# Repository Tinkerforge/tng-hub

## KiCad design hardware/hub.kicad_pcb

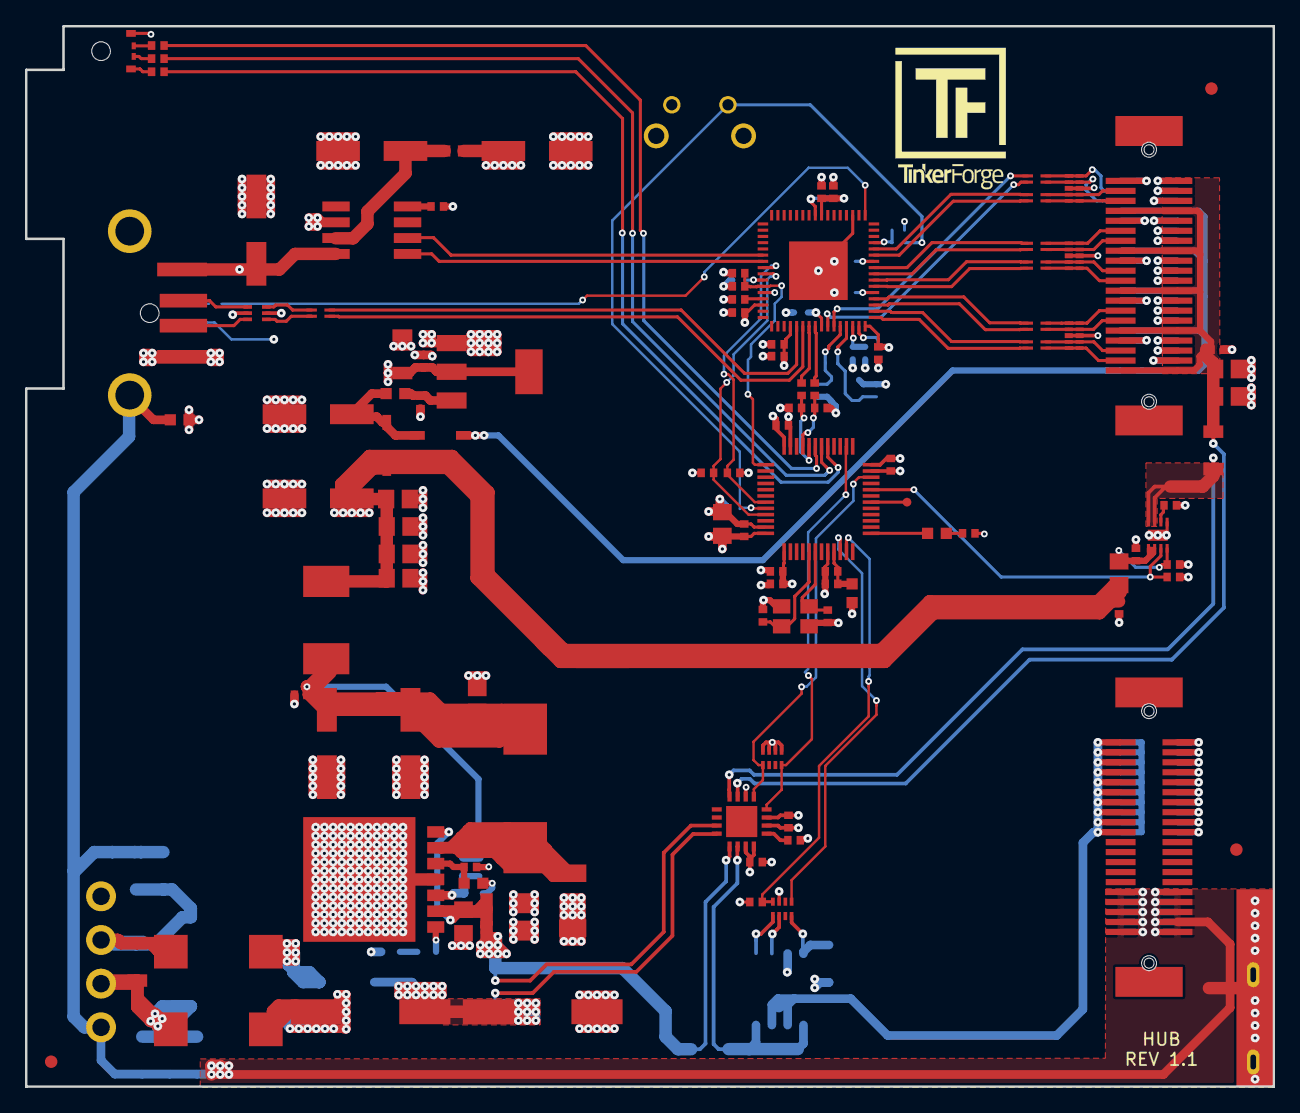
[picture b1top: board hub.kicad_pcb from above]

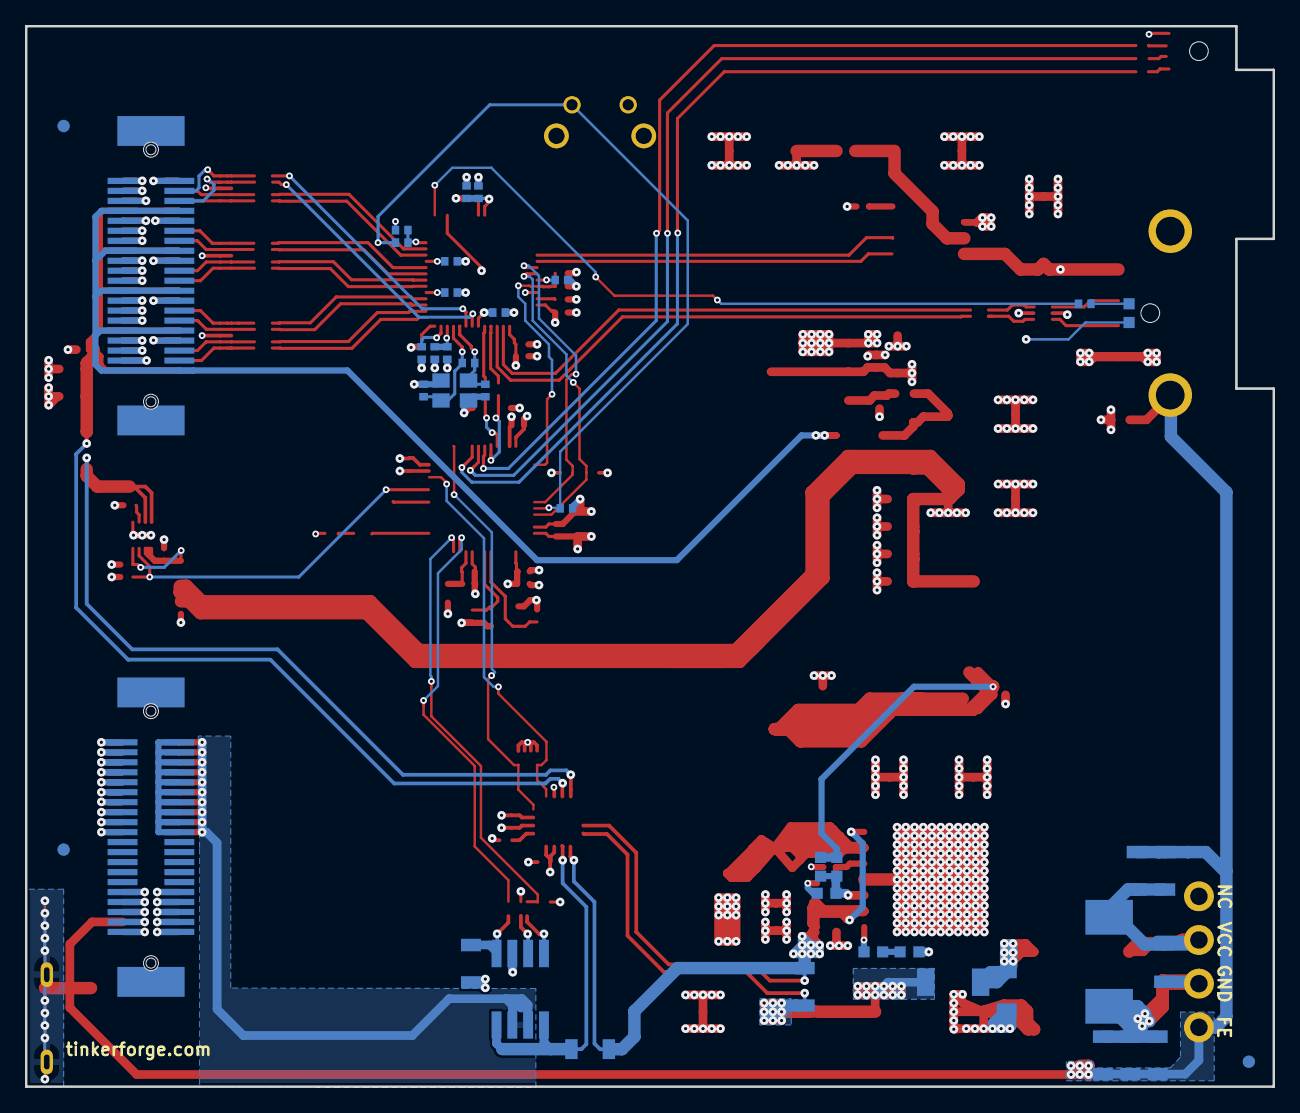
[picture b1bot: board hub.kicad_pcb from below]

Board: 4 copper layers, 100.0 x 85.0 mm, 152 parts (41 on the bottom side), 99 nets.

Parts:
C101, C102, C137, C138: 33pF; C0402F
C103, C105, C115, C119, C123, C124, C125, C126, C128, C134, C209, C226: 1uF; C0402F
C104, C106, C107, C110, C111, C112, C113, C114, C116, C118, C127, C129, C130, C131, C133, C214, C221, C222: 100nF; C0402F
C108, C109, C117, C203, C216, C219, C220: 100uF; ELKO_63
C120: 100nF; C0603F
C121, C122: 47pF; C0402F
C132: DNP; C0402F
C135, C136, C139, C215, C218, C223, C224, C225: 10uF; C0805E
C201, C202: 10uF/35V; C1206
C204, C211: 10nF; C1206
C205: 100nF/35V; C0805E
C206, C207: 1nF 2kV; C1206
C208: 100pF; C0402F
C210: 4.7nF; C0603F
C212, C213: UWT1H221MNL1GS; ELKO_103
C217: DNP; C0603F
C227: 10uF; C1206
D101: LED green; LED-LP
D102: LED; D0603F
D201: 3.0SMI30CATR; SMC
D202, D203: B0520LW-7-F; SOD-123
D205, D206: PMEG6045; SOD-128
Fiducial_Mark: VAL**; Fiducial_Mark
Fiducial_Mark#2, Fiducial_Mark#3, Fiducial_Mark#4, Fiducial_Mark#5, Fiducial_Mark#6: VAL**; Fiducial_Mark
J101: USB-A; USB-A-SMT-8231
J102: TNG-Power-BTM; TNG-40-BTM
J103: TNG-Power-TOP; TNG-40-TOP
J104: TNG-Data-BTM; TNG-40-BTM
J105: TNG-Data-TOP; TNG-40-TOP
L101, L201: INDUCTs; R0603F
L102, L103, L104, L105, L106, L107, L110: 744230900; WE-CNSW-0603
L108: FB; R0603F
L109: 742792040; R0805E
L202: 22uH 74437368220; WE-LHMI
L203: 10uH; SRP7030
LED101: EASV3015RGBA0; LED-RGB-LP
P101: Debug; DEBUG_PAD
P102: PE; PE_Hook
P202: PWR IN; OQ_4P
R101, R105, R106, R107, R109, R111, R116, R117, R218: 10k; R0402F
R102: 100k; R0402F
R103: 1M; R0402F
R104, R108, R114, R121: 1k; R0402F
R110: 12k; R0402F
R112, R113: 22; R0402F
R115, R119: 0; R0402F
R118: 1k; R1206
R120: 56; R0402F
R204, R206, R207: VC1206K201R030; R1206
R208: 27k; R0603F
R209: 1M; R1206
R212: 20k; R0603F
R214: 47k; R0603F
R215: 8.2k; R0603F
R219, R220, R221: 0.02; R1206
RP102, RP201: 10k; 4X0402
SW101: BOOT; TACT-6MM-HOR
T201: 744272251; WE-SL5
U101: USB2517; QFN64-9x9mm-0.5mm_USB2517
U102: MIC2026-1YM; SO-8
U103: 82400152; SOT563-SPEC
U104: STM32F070CBT6; LQFP48
U105, U106, U107: TPD4S010DQA
U110: TPS22975; WSON8-2x2
U112: VN7140AS; SO-8
U201: AZ1117EH; SOT-223
U203: BD90640HFP; BD906XX-C-HRP7
U204: PAC1933; QFN-16
X101: 24MHz; CRYSTAL_3225
X102: 8MHz; CRYSTAL_3225

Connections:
3V3: C110.1, C111.1, C112.1, C113.1, C114.1, C115.1, C116.1, C118.1, C119.1, C123.1, C127.1, C129.1, C130.1, C131.1, C139.1, C221.1, C222.1, C226.1, C227.1, D101.1, L108.1, LED101.1, R101.2, R102.2, R106.2, R111.2, R116.2, R117.2, R121.2, RP102.7, RP201.1, RP201.2, RP201.3, RP201.4, SW101.1, U101.5, U101.10, U101.24, U101.44, U101.46, U101.52, U101.57, U101.64, U104.1, U104.24, U104.36, U104.48, U201.2, U204.2, U204.6, U204.15, U204.16
5V_STACK_UP: D202.1, J104.7, J104.8, J104.15, J104.16, J104.23, J104.24, J104.31, J104.32, J104.39, J104.40
+5V: C108.1, C125.2, C218.1, C219.1, C223.1, C224.1, C225.1, D203.1, L101.2, L109.1, L203.2
BOOT: R108.2, R114.2, SW101.2, U104.44
CTRL_USB_D+: C122.1, R112.2, U104.33
CTRL_USB_D-: C121.1, R113.2, U104.32
CUR1+: C212.1, C213.1, D205.2, R219.1, U204.12
CUR1-: C201.1, C202.1, C205.1, R219.2, R220.1, U203.2, U203.7, U204.11, U204.13
CUR2-: R220.2, U112.5, U112.8, U204.14
CUR3+: R221.1, U110.7, U110.8, U204.8
CUR3-: C134.2, C135.2, C136.2, J105.7, J105.8, J105.15, J105.16, J105.23, J105.24, J105.31, J105.32, J105.39, J105.40, R221.2, U204.7
EXT_USB_D+: L102.1, U101.54
EXT_USB_D-: L102.4, U101.53
EXT_USB_D_F+: J101.3, U103.6
EXT_USB_D_F-: J101.2, U103.4
Earth: C120.1, C206.2, C207.1, J101.SHD, J102.31, J102.32, J102.33, J102.34, J102.35, J102.36, J102.37, J102.38, J102.39, J102.40, J103.31, J103.32, J103.33, J103.34, J103.35, J103.36, J103.37, J103.38, J103.39, J103.40, P102.1, P202.4, R206.2, R207.1, R209.1
GND: C101.2, C102.2, C103.2, C104.2, C105.2, C106.2, C107.2, C108.2, C109.2, C110.2, C111.2, C112.2, C113.2, C114.2, C115.2, C116.2, C117.2, C118.2, C119.2, C120.2, C121.2, C122.2, C123.2, C124.2, C125.1, C126.1, C127.2, C128.2, C129.2, C130.2, C131.2, C132.2, C133.2, C134.1, C135.1, C136.1, C137.1, C138.1, C139.2, C201.2, C202.2, C203.2, C205.2, C208.2, C209.2, C210.2, C211.2, C212.2, C213.2, C214.2, C215.2, C216.2, C218.2, C219.2, C220.2, C221.2, C222.2, C223.2, C224.2, C225.2, C226.2, C227.2, D206.1, J101.4, J102.1, J102.3, J102.5, J102.7, J102.9, J102.11, J102.13, J102.15, J102.17, J102.19, J103.2, J103.4, J103.6, J103.8, J103.10, J103.12, J103.14, J103.16, J103.18, J103.20, J104.1, J104.2, J104.3, J104.5, J104.9, J104.10, J104.11, J104.13, J104.17, J104.18, J104.19, J104.21, J104.25, J104.26, J104.27, J104.29, J104.33, J104.34, J104.35, J104.37, J105.1, J105.2, J105.4, J105.6, J105.9, J105.10, J105.12, J105.14, J105.17, J105.18, J105.20, J105.22, J105.25, J105.26, J105.28, J105.30, J105.33, J105.34, J105.36, J105.38, R105.1, R107.2, R109.2, R110.1, R114.1, R118.1, R208.1, R215.1, R218.2, T201.3, U101.19, U101.EXP, U102.6, U103.2, U104.8, U104.23, U104.35, U104.47, U105.3, U105.8, U106.3, U106.8, U107.3, U107.8, U110.5, U110.EXP, U112.3, U201.1, U203.4, U203.EXP, U204.3, X101.3, X102.3
LEDB: R120.1, U104.31
LEDG: R119.1, U104.30
LEDR: R115.1, U104.29
unnamed: C101.1, R103.2, U101.61, X101.1
unnamed: C102.1, R103.1, U101.60, X101.2
unnamed: C103.1, C104.1, U101.25
unnamed: C105.1, C106.1, U101.62
unnamed: C109.1, L101.1, U102.7
unnamed: C124.1, C133.1, L108.2, U104.9
unnamed: C126.2, C128.1, L109.2, U110.1, U110.2, U110.4
unnamed: C132.1, U110.6
unnamed: C137.2, U104.5, X102.2
unnamed: C138.2, U104.6, X102.1
unnamed: C203.1, D202.2, D203.2, L201.1
unnamed: C204.1, C206.1, D201.1, P202.2, R204.1, R206.1, T201.1
unnamed: C204.2, C207.2, D201.2, P202.3, R204.2, R207.2, R209.2, T201.2
unnamed: C208.1, R208.2, U203.5
unnamed: C209.1, L201.2, U201.3
unnamed: C210.1, R212.1
unnamed: C211.1, D205.1, T201.4
unnamed: C214.1, C215.1, C216.1, C217.1, C220.1, L202.2, L203.1, R214.2
unnamed: C217.2, R214.1, R215.2, U203.3
unnamed: D101.2, R104.2
unnamed: D102.1, R121.1
unnamed: D102.2, U104.13
unnamed: D206.2, L202.1, U203.6
unnamed: J102.2, J102.4, J102.6, J102.8, J102.10, J102.12, J102.14, J102.16, J102.18, J102.20
unnamed: J104.4, L110.2, U105.1, U105.10
unnamed: J104.6, L110.3, U105.2, U105.9
unnamed: L102.2, U103.1
unnamed: L102.3, U103.3
unnamed: LED101.2, R120.2
unnamed: LED101.3, R119.2
unnamed: LED101.4, R115.2
unnamed: P101.1, U104.18
unnamed: R101.1, U101.45
unnamed: R104.1, U101.17
unnamed: R105.2, U102.4
unnamed: R107.1, U101.42
unnamed: R108.1, R109.1, U101.13
unnamed: R110.2, U101.63
unnamed: R112.1, U101.56
unnamed: R113.1, U101.55
unnamed: R118.2, RP102.4, U112.4
unnamed: R212.2, U203.1
unnamed: R218.1, U204.1
unnamed: RP102.1, U112.1
unnamed: RP102.2, U112.2
unnamed: U101.38, U102.2
unnamed: U101.39, U102.1
PAC_SCL: RP201.8, U104.26, U204.4
PAC_SDA: RP201.5, U104.22, U204.5
STACKPWR: J103.1, J103.3, J103.5, J103.7, J103.9, J103.11, J103.13, J103.15, J103.17, J103.19, U112.6, U112.7
STACK_USB_D0+: L103.1, U101.12
STACK_USB_D0-: L103.4, U101.11
STACK_USB_D0_F+: J105.3, L103.2, U105.4, U105.7
STACK_USB_D0_F-: J105.5, L103.3, U105.5, U105.6
STACK_USB_D1+: L104.1, U101.9
STACK_USB_D1-: L104.4, U101.8
STACK_USB_D1_F+: J105.11, L104.2, U106.5, U106.6
STACK_USB_D1_F-: J105.13, L104.3, U106.4, U106.7
STACK_USB_D2+: L105.1, U101.7
STACK_USB_D2-: L105.4, U101.6
STACK_USB_D2_F+: J105.19, L105.2, U106.2, U106.9
STACK_USB_D2_F-: J105.21, L105.3, U106.1, U106.10
STACK_USB_D3+: L106.1, U101.4
STACK_USB_D3-: L106.4, U101.3
STACK_USB_D3_F+: J105.27, L106.2, U107.5, U107.6
STACK_USB_D3_F-: J105.29, L106.3, U107.4, U107.7
STACK_USB_D4+: L107.1, U101.2
STACK_USB_D4-: L107.4, U101.1
STACK_USB_D4_F+: J105.35, L107.2, U107.2, U107.9
STACK_USB_D4_F-: J105.37, L107.3, U107.1, U107.10
SW_5_ENABLE: R116.1, U104.20, U110.3
SW_24_CUR: RP102.5, U104.10
SW_24_ENABLE: R117.1, RP102.8, U104.11
UP_USB_D+: L110.1, U101.59
UP_USB_D-: L110.4, U101.58
USB-PWR: C117.1, J101.1, U102.8, U103.5
USB_RESET: C107.1, R102.1, U101.43, U104.37
USB_SMB_CLK: R111.1, U101.41, U104.45
USB_SMB_DATA: R106.1, U101.40, U104.43

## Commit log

2019-12-06 hub module finished
2019-12-23 update rgb led drill diameter
2019-12-30 fix inductor footprint
2020-01-02 add stuff
2020-01-14 fix 3d settings
2020-03-02 fix drc errors
2020-03-02 add hook footprint
2020-03-03 fix power routing
2020-03-03 add earth plane
2020-03-27 fix resistor value, put usb tht connectors in paste layer
2020-05-14 fix value
2020-05-14 Add HUB stub firmware
2020-06-19 Add USB2517 datasheet
2020-06-22 fix signal names
2020-06-24 fix usb hub boot issue
2020-07-21 Add initial support for USB2517 hub IC
    Currently just writes a dummy configuration to the hub
2020-07-27 Use HAL Config from bricklib2
2020-07-27 Add TIM defines for status LEDs
2020-09-04 add version 1.2
    * fix footprints
2020-09-07 fix values
2020-09-07 fix stuff
2020-09-07 fix footprints
2020-09-08 fix footprint
2020-09-08 update all footprints
2020-09-09 fix outline
2020-09-10 fix usb connector position, fix 3d stuff

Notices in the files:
hardware/hub.kicad_pcb:
Licensed under CERN OHL v.1.1
Copyright (©) 2020, B.Nordmeyer
Copyright Tinkerforge GmbH 2020.
This documentation describes Open Hardware and is licensed under the
CERN OHL v. 1.1.
